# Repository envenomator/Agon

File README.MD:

[Agon supplemental programmers documentation Wiki](https://github.com/envenomator/Agon/wiki)

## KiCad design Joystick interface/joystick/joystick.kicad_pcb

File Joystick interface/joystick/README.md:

# Agon Joystick interface

## PINOUT ESP32
- DATA -> ESPI35
- LATCH <- ESPIO26
- CLK <- ESPIO27

## PINOUT ez80
- DATA -> PC1 
- LATCH <- PC2
- CLK <- PC0

## To do
- Order a PCB with the option 'specify location for order number', sigh
- Solder the headers straight next time
- Remove the ESP32 side as this will not be used in the future
- Create some sort of 3d printed bracket/housing for the connector

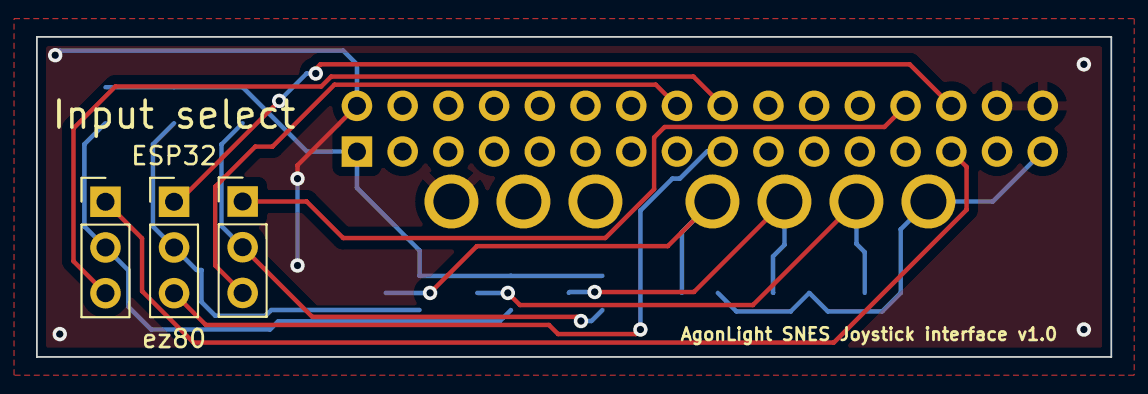
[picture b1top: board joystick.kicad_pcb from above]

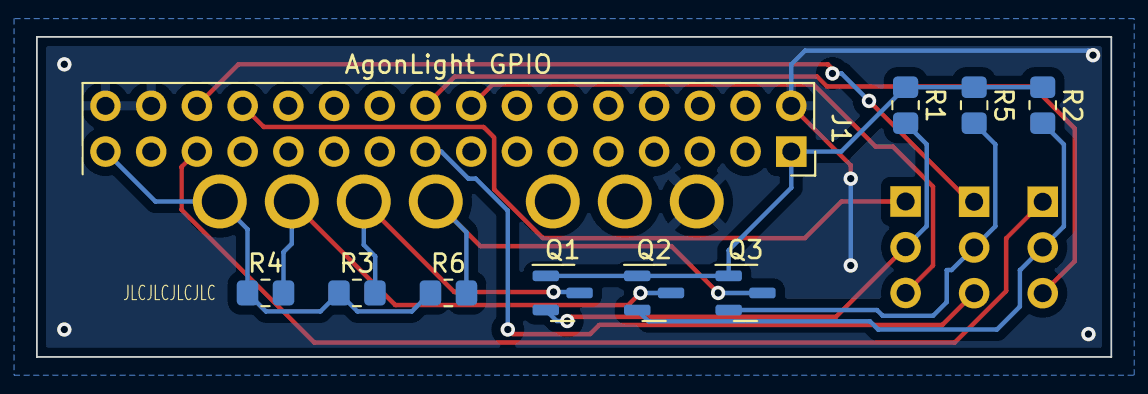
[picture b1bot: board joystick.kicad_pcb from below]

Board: 2 copper layers, 59.7 x 17.8 mm, 14 parts (10 on the bottom side), 15 nets.

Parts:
J1: AgonLight GPIO; PinSocket_2x16_P2.54mm_Vertical
JP1, JP2, JP3: Jumper_3_Open; PinHeader_1x03_P2.54mm_Vertical
Q1, Q2, Q3: BSS138; SOT-23
R1, R2, R3, R4, R5, R6: R; R_0805_2012Metric_Pad1.20x1.40mm_HandSolder
U1: SNES

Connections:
+3.3V: J1.1, Q1.1 (G), Q2.1 (G), Q3.1 (G), R1.1, R2.1, R5.1
+5V: J1.31, R3.1, R4.1, R6.1, U1.1 (VCC)
/CLOCK: Q2.3 (D), R4.2, U1.2 (CLOCK)
/CLOCK_SELECT: JP1.2 (C), Q2.2 (S), R2.2
/DATA: Q3.3 (D), R6.2, U1.4 (DATA1/2)
/DATA_SELECT: JP2.2 (C), Q3.2 (S), R5.2
/ESPI35: J1.28, JP2.1 (A)
/ESPIO26: J1.26, JP3.1 (A)
/ESPIO27: J1.27, JP1.1 (A)
/LATCH: Q1.3 (D), R3.2, U1.3 (LATCH)
/LATCH_SELECT: JP3.2 (C), Q1.2 (S), R1.2
/PC0: J1.18, JP1.3 (B)
/PC1: J1.17, JP2.3 (B)
/PC2: J1.16, JP3.3 (B)
GND: J1.2, J1.30, J1.32, U1.7 (GND)

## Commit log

2022-07-31 ESP32 VDU working API
2022-07-31 Removed unused routines
2022-07-31 API description
2022-07-31 VDU client code added
2022-07-31 AgonLight case added
2022-07-31 Example Mandelbrot added
2022-07-31 Sprite test code provided as example
2022-07-31 Sokobanprep / reader complete
2022-08-02 Alpha sokoban added - opens 'levels.bin' and displays on screen
2022-08-02 bugfix in righttrim
2022-08-02 crlf removal in sokobanprep
2022-08-03 Rewritten sokobanprep
2022-08-05 All bitmaps present, beta colors
2022-08-05 .piskel files added
2022-08-06 Sprites correctly showing
2022-08-06 Bugfixes done
2022-08-06 Original level included
2022-08-06 VDU correctly accepts MoveBy(x,y)
2022-08-10 Joystick interface added, code and PCB
2022-08-28 Joystick images added
2022-08-28 Joystick readme
2022-10-20 Sokoban splash logo
2022-10-21 Helloworld loadable
2022-10-21 puts in assembly
2022-10-22 Loadable sprite code done
2022-10-22 Correct vblank waiting
2022-10-22 Deleted old stuff, changed README to reflect current sprite API
2022-10-22 Cleanup
2022-10-22 Cleanup main.c comments
2022-10-22 typo fixed
2022-10-22 mos_f* functions added to example
2022-10-23 New memory map with internal 8KB RAM
2022-10-24 Hexload patch in ez80 assembly
2022-10-25 send.py sends hexfiles to serial port, default COM3'
2022-10-25 vdp/mos patches extended for new functions in vdp 1.02
2022-10-28 Working hexload patch
2022-10-28 Patch README added
2022-10-28 Patch README addendum
2022-10-28 Patch RAM start explained in README
2022-10-28 Final typo removed
2022-10-31 Hello world in assembly, barebones example
2022-10-31 Changed dir name
2022-11-01 SNES Joystick reader example added
2022-11-01 Joystick README updated
2022-11-06 Libraries added
2022-11-06 delayms function added in libraries, example 500Hz code
2022-11-26 hexload implemented as command to MOS 1.02
2022-11-26 hexload - better indication of errors during transfer
2022-12-09 bugfix in getch
2022-12-10 New Sokoban loadable
2022-12-10 Splash screen
2022-12-10 Error message included if no levels loading
2022-12-11 Working Sokoban loadable game
2022-12-11 Sokoban release
2022-12-11 Cleanup old files
2022-12-16 Firmware upgrade beta
2022-12-16 fwupgr new function writeflash dest/src/size
2022-12-17 Agon MOS firmware upgrade utility release
2022-12-17 Readme added
2022-12-18 Legacy flash for 1.01 to 1.02 added
2022-12-18 flash_legacy also working from 1.00
2022-12-18 flash_legacy code commented
2022-12-18 Readme
2022-12-18 VDP flashable batchfiles included with precompiled binaries
2022-12-18 Fullkeycode example in scratch, plus template
2022-12-20 Sokoban auto-advance bugfix
2022-12-20 Sokoban bugfix release, circular undo buffer
2022-12-26 I2C test code
2022-12-27 I2C MR test code in place
2022-12-27 I2C MT sendstop timer included in ISR
2022-12-27 I2C MT bus error 00h sends stop now
2022-12-27 I2C MR receive code in test
2022-12-27 I2C MR seems to work, finally, debugging code still in place
2022-12-27 I2C anonymous labels in use
2022-12-27 I2C several bugfixes, receiving multiple bytes works
2022-12-27 I2C code in separate files now
2022-12-27 I2C errorcodes complete
2022-12-27 I2C All constants defined, only anonymous labels in loops
2022-12-27 I2C code cleanup - DEBUG code still present
2022-12-27 I2C errors now returned to MOS callers
2022-12-27 I2C iw/ir demo code as MOS cmd, LED slave switches to 0/1
2022-12-28 Agontimer 100us timer - delay100us
2022-12-28 I2C test with barebones 1602 code, not all LCD functions working
2022-12-28 I2C excel sheet for I2C_CCR added, clockbug fixed, DEBUG commented out, bug in >30 INTs caused by DEBUG code
2022-12-28 I2C 1602 backlight set back to each command. Change in mos.c demo code
2022-12-28 I2C bugfix in interrupt handler for AR-NACK case, re-arranged interrupt code, removed all debug code
2022-12-28 1602 Clear command now correctly using code 0x01
2022-12-28 I2C_SetFrequency() function added, default is 57.6Khz, 3 options in i2c.h
2022-12-28 I2C JR/JP optimization in interrupt
2022-12-28 I2C mbindex++ optimization in interrupt
2022-12-28 I2C completed error state feedback in all NACK cases
2022-12-29 I2C changed interrupt to use CALL/switch DW table. Too many entries using CP/JR going forward
2022-12-29 I2C initial DHT20 library conversion to C done, 0 errors on compile, no demo yet
2022-12-29 I2C DHT20 demo code in
2022-12-29 I2C DHT20 with demo code at 230Khz, working perfectly
2022-12-29 I2C cleanup readme files
2023-01-06 UART1 - testcode working
2023-01-10 Library bugfixes for getsysvar_cursorX/Y and new getsysvar_scrchar
2023-01-12 Removed old hexload, migrated to new public repo
2023-01-14 Moved flash to separate repository, added hyperlink in README
2023-01-14 Changed README
2023-01-14 Moved sokoban to dedicated repo
2023-01-21 MOS set_vector() and MOS_SV_check() added to mos libraries
2023-01-22 timer0 freerunning mode added in Agontimer interface library
2023-01-22 loadable pulsegenerator in scratch
2023-01-22 timer0 volatile added, to avoid blackeye using it in C
2023-02-19 stdint.h created to match ez80 compiler types
2023-02-23 Added mos_save and mos_del to the mos-interface.asm and mos-interface.h
2023-03-02 Created MOS cmd loader, calling &40000 after loading a module to this address
2023-03-02 Clarified memory map, according to MOS 1.02 allocation
2023-03-03 CLS utility provided
2023-03-20 Updated template to use new library code and updated init.asm
2023-03-20 Updated init.asm in template
2023-03-23 Updated VDP commands to use MOS 1.03 constants for VDP 23,0,n
2023-03-25 Library/template code updated for MOS 1.03
2023-03-25 Cleanup for MOS 1.03
2023-03-26 Added pagedMode function in vdp.h/vdp.c
2023-03-26 setPaletteColor supported in vdp
2023-03-29 Fixed vdp_spriteSetFrame() bug - Thanks to james7780
2023-03-30 Library code for mos_uopen/mos_uclose/mos_ugetc/mos_uputc
2023-04-04 mos_setintvector bugfix in mos-interface.asm
2023-04-10 Timer0 using mos_setintvector now / demo in scratch
2023-04-10 Freerunning example
2023-04-15 VDP colour functions matching VDP 1.03 API
2023-04-16 Added MOS 1.03RC4 mos_fread/mos_fwrite/mos_flseek
2023-04-17 fread/fwrite return value fix
2023-04-18 mos_flseek fix
2023-04-19 mos_getfil and FIL structure provided in C
2023-04-21 Structures for FFOBJID / FIL tested by Greg Dyke
2023-04-23 .vscode tasks in template
2023-05-20 Moved Sprite API to Wiki
2023-05-20 Wiki link in README
2023-05-26 Annotated example
2023-05-27 101 example
2023-05-27 ez80asm example code 2
2023-05-27 Changed SPL to 24bit in ez80 register overview png
2023-05-27 ez80asm example 3 - string loops
2023-06-04 Joystick example in ez80asm
2023-09-30 VDP 1.04 screenmodes in vdp.h
2023-10-06 mos_api.inc adapted for ez80asm
2023-10-06 MOS EXIT codes in mos_api.inc
2023-10-06 CLS program based on ez80asm code
2023-10-06 crc32 program complete
2023-10-10 num2string 24-bit routines
2023-10-10 New flash program in scratch
2023-10-29 Console8 joystick stuff
2023-10-29 Console8 joystick test complete
2023-10-30 Template updated, moved old joystick code to SNES joystick
2023-10-30 Project clone script
2023-10-30 vscode template build update
2023-10-30 Console8 joystick test program
2023-10-30 send.py DTR/RTS low
2023-11-10 I2C test program
2023-11-12 Nunchuck test
2023-11-17 Nunchuck example program done
2023-11-18 Nunchuck demo ported to AgDev
2024-03-18 Added schematics for several Agon variants
